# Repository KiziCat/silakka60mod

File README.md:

# Silakka60mod

This is my attempt at creating split keyboard based on the silakka54 with separate left and right pcb's, additional keys and slightly modified layout. 
WIP!

So far it is a outcome of one day speed run learning about laying out pcb's and how to use kicad so i would not try to use it just yet.

Hey, If you would like to order pcb's from aivon using my link it would be huge help to me https://www.aivon.com/?Mb_InviteId=29714

# Silakka54

Silakka54 is a RP2040 Zero based 54-key column staggered split keyboard. PCB uses hotswap sockets. Design is inspired from REVIUNG41 and Corne keyboards.

PCB is designed for MX style key switches. Current top plate only supports MX style switches. 5-pin switches are supported. I recommend using Vial firmware.

**For more information visit https://github.com/Squalius-cephalus/silakka54/wiki**

PCB design uses footprints from [ScottoKeebs](https://github.com/joe-scotto/scottokeebs/tree/main/Extras/ScottoKicad "ScottoKeebs") and [kbd library.](https://github.com/foostan/kbd "kbd library.")

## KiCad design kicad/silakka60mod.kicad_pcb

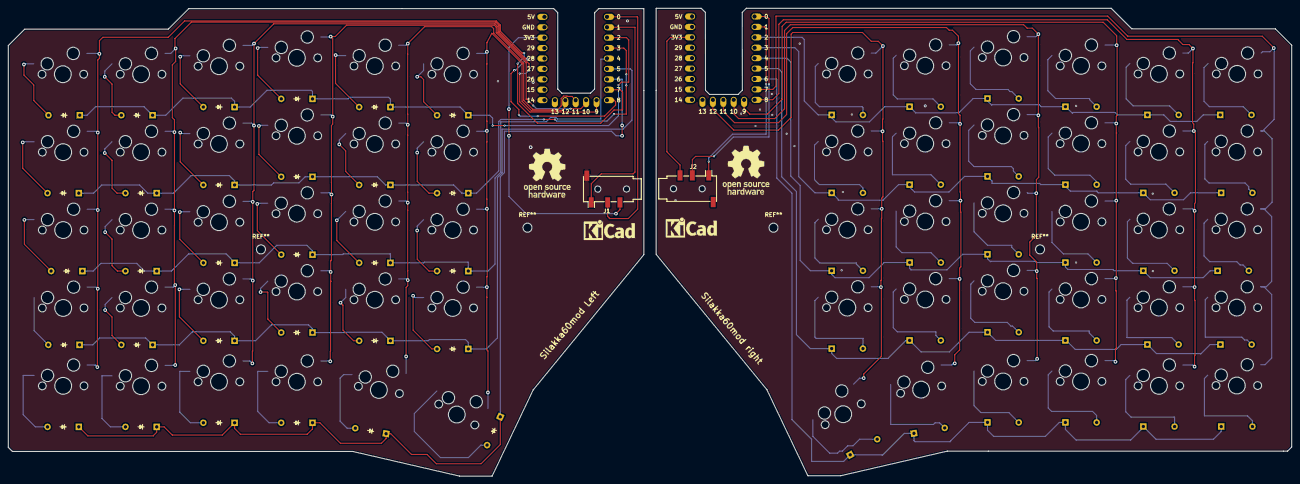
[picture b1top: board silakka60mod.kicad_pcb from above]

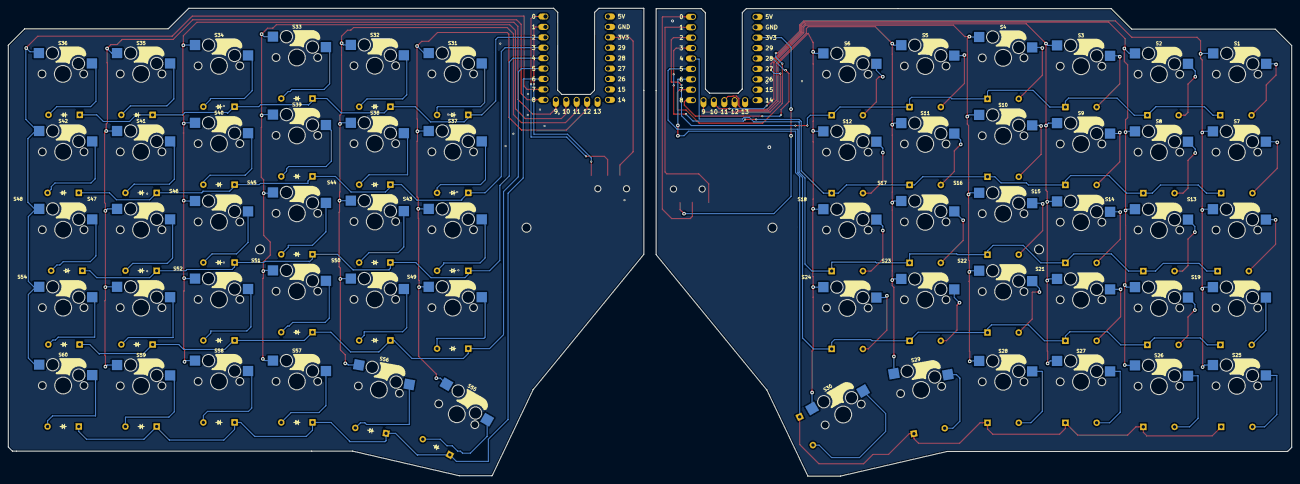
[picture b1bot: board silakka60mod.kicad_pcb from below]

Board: 2 copper layers, 313.0 x 114.1 mm, 124 parts (90 on the bottom side), 90 nets.

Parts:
D1, D2, D3, D4, D5, D6, D7, D8, D9, D10, D11, D12, D13, D14, D15, D16, D17, D18, D19, D20, D21, D22, D23, D24, D25, D26, D27, D28, D29, D30, D31, D32, D33, D34, D35, D36, D37, D38, D39, D40, D41, D42, D43, D44, D45, D46, D47, D49, D49#2, D50, D51, D52, D53, D54, D55, D56, D57, D58, D59, D60: Diode; Diode_DO-35
J1, J2: AudioJack4; Jack_3.5mm_PJ320D_Horizontal
S1, S2, S3, S4, S5, S6, S7, S8, S9, S10, S11, S12, S13, S14, S15, S16, S17, S18, S19, S20, S21, S22, S23, S24, S25, S26, S27, S28, S29, S30, S31, S32, S33, S34, S35, S36, S37, S38, S39, S40, S41, S42, S43, S44, S45, S46, S47, S48, S49, S50, S51, S52, S53, S54, S55, S56, S57, S58, S59, S60: Keyswitch; keyswitch_cherrymx_hotswap_1u
U1, U2: RP2040_Zero

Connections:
COL0: S1.2, S7.2, S13.2, S19.2, S25.2, U1.8 (7)
COL0b: S36.2, S42.2, S48.2, S54.2, S60.2, U2.8 (7)
COL1: S2.2, S8.2, S14.2, S20.2, S26.2, U1.9 (8)
COL1b: S35.2, S41.2, S47.2, S53.2, S59.2, U2.9 (8)
COL2: S3.2, S9.2, S15.2, S21.2, S27.2, U1.10 (9)
COL2b: S34.2, S40.2, S46.2, S52.2, S58.2, U2.10 (9)
COL3: S4.2, S10.2, S16.2, S22.2, S28.2, U1.11 (10)
COL3b: S33.2, S39.2, S45.2, S51.2, S57.2, U2.11 (10)
COL4: S5.2, S11.2, S17.2, S23.2, S29.2, U1.12 (11)
COL4b: S32.2, S38.2, S44.2, S50.2, S56.2, U2.12 (11)
COL5: S6.2, S12.2, S18.2, S24.2, S30.2, U1.13 (12)
COL5b: S31.2, S37.2, S43.2, S49.2, S55.2, U2.13 (12)
GND: J1.S, U1.22 (GND), U2.22 (GND)
unnamed: D1.2 (A), S1.1
unnamed: D2.2 (A), S2.1
unnamed: D3.2 (A), S3.1
unnamed: D4.2 (A), S4.1
unnamed: D5.2 (A), S5.1
unnamed: D6.2 (A), S6.1
unnamed: D7.2 (A), S7.1
unnamed: D8.2 (A), S8.1
unnamed: D9.2 (A), S9.1
unnamed: D10.2 (A), S10.1
unnamed: D11.2 (A), S11.1
unnamed: D12.2 (A), S12.1
unnamed: D13.2 (A), S13.1
unnamed: D14.2 (A), S14.1
unnamed: D15.2 (A), S15.1
unnamed: D16.2 (A), S16.1
unnamed: D17.2 (A), S17.1
unnamed: D18.2 (A), S18.1
unnamed: D19.2 (A), S19.1
unnamed: D20.2 (A), S20.1
unnamed: D21.2 (A), S21.1
unnamed: D22.2 (A), S22.1
unnamed: D23.2 (A), S23.1
unnamed: D24.2 (A), S24.1
unnamed: D25.2 (A), S25.1
unnamed: D26.2 (A), S26.1
unnamed: D27.2 (A), S27.1
unnamed: D28.2 (A), S28.1
unnamed: D29.2 (A), S29.1
unnamed: D30.2 (A), S30.1
unnamed: D31.2 (A), S31.1
unnamed: D32.2 (A), S32.1
unnamed: D33.2 (A), S33.1
unnamed: D34.2 (A), S34.1
unnamed: D35.2 (A), S35.1
unnamed: D36.2 (A), S36.1
unnamed: D37.2 (A), S37.1
unnamed: D38.2 (A), S38.1
unnamed: D39.2 (A), S39.1
unnamed: D40.2 (A), S40.1
unnamed: D41.2 (A), S41.1
unnamed: D42.2 (A), S42.1
unnamed: D43.2 (A), S43.1
unnamed: D44.2 (A), S44.1
unnamed: D45.2 (A), S45.1
unnamed: D46.2 (A), S46.1
unnamed: D47.2 (A), S47.1
unnamed: D49#2.2 (A), S48.1
unnamed: D49.2 (A), S49.1
unnamed: D50.2 (A), S50.1
unnamed: D51.2 (A), S51.1
unnamed: D52.2 (A), S52.1
unnamed: D53.2 (A), S53.1
unnamed: D54.2 (A), S54.1
unnamed: D55.2 (A), S55.1
unnamed: D56.2 (A), S56.1
unnamed: D57.2 (A), S57.1
unnamed: D58.2 (A), S58.1
unnamed: D59.2 (A), S59.1
unnamed: D60.2 (A), S60.1
ROW0: D1.1 (K), D2.1 (K), D3.1 (K), D4.1 (K), D5.1 (K), D6.1 (K), U1.3 (2)
ROW0b: D31.1 (K), D32.1 (K), D33.1 (K), D34.1 (K), D35.1 (K), D36.1 (K), U2.3 (2)
ROW1: D7.1 (K), D8.1 (K), D9.1 (K), D10.1 (K), D11.1 (K), D12.1 (K), U1.4 (3)
ROW1b: D37.1 (K), D38.1 (K), D39.1 (K), D40.1 (K), D41.1 (K), D42.1 (K), U2.4 (3)
ROW2: D13.1 (K), D14.1 (K), D15.1 (K), D16.1 (K), D17.1 (K), D18.1 (K), U1.5 (4)
ROW2b: D43.1 (K), D44.1 (K), D45.1 (K), D46.1 (K), D47.1 (K), D49#2.1 (K), U2.5 (4)
ROW3: D19.1 (K), D20.1 (K), D21.1 (K), D22.1 (K), D23.1 (K), D24.1 (K), U1.6 (5)
ROW3b: D49.1 (K), D50.1 (K), D51.1 (K), D52.1 (K), D53.1 (K), D54.1 (K), U2.6 (5)
ROW4: D25.1 (K), D26.1 (K), D27.1 (K), D28.1 (K), D29.1 (K), D30.1 (K), U1.7 (6)
ROW4b: D55.1 (K), D56.1 (K), D57.1 (K), D58.1 (K), D59.1 (K), D60.1 (K), U2.7 (6)
RX: J1.T, U1.2 (1)
RXb: J2.T, U2.2 (1)
TX: J1.R1, U1.1 (0)
TXb: J2.R1, U2.1 (0)
VCC: J1.R2, U1.21 (3V3)
VCCb: J2.R2, U2.21 (3V3)
un: U2.14 (13), U2.15 (14), U2.16 (15), U2.17 (26), U2.18 (27), U2.19 (28), U2.20 (29), U2.23 (5V)
